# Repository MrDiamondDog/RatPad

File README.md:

# RatPad

My own personal (rat-themed) hackpad! Featuring a decorative 4x4 RGB LED matrix, an informational screen, rats, and a ton of keys to control anything with!

The goal of this project is to learn! I have been wanting experience with PCBs, Fusion, and soldering for a while and this is a good
all-in-one project to get that experience at no cost to me.

Part of Hack Club's Blueprint YSWS.

## Features

- 12 Keys.
- 4x4 RGB LED Matrix.
- 0.91in OLED display.
- Multiple layers, programmable keys, etc.
- LED Matrix for cool decoration. No practical purpose.
- A rat drawn on the silkscreen of the PCB.
- Black + Blue theme
- KMK Firmware

## Todo

- [x] Schematic
- [x] Routing PCB
- [x] Case Design
- [x] Basic Firmware
- [ ] Get Physical Items
- [ ] Solder PCB
- [ ] Finished Build!

## PCB

Here's the schematic and routed PCB! There's a lot of stuff on the silkscreen for fun and the LEDs and keys are both routed in matrices to save on GPIOs! In fact, I have one GPIO available still!

I decided to do chamfered edges on all the corners, with a big one in the lower left since I had extra space and figured it would look nice.

I've also included M3 screw holes, I don't think I'll be using them though.

I definitely should have added a ground plane, but it should be fine.

## Case

Here's all the images of the case! There's a window on the left of the lid to see all the interesting electronics, silkscreen, and LED matrix, a hole for the OLED, and all the holes for the keys.

The chamfered edges from the PCB are reflected on the case as well.

The lid is held on with 4 M3 screws.

I would love to add some acrylic to the window and/or oled, but I don't have access to a laser cutter or any acrylic in the first place.

## BOM

| Item | Quantity |
| ---- | -------- |
| PCB | 1 |
| Through-Hole Seeed XIAO RP2040 | 1 |
| MX Style Switches | 12 |
| DSA Keycaps | 12 |
| Through-Hole IN4148 Diodes | 12 |
| 0.91in OLED I2C Display | 1 |
| SK6812 MINI-E LEDs | 16 |
| M3x16mm Screws | 4 |
| 3d Printed Parts (case + lid) | 2 |

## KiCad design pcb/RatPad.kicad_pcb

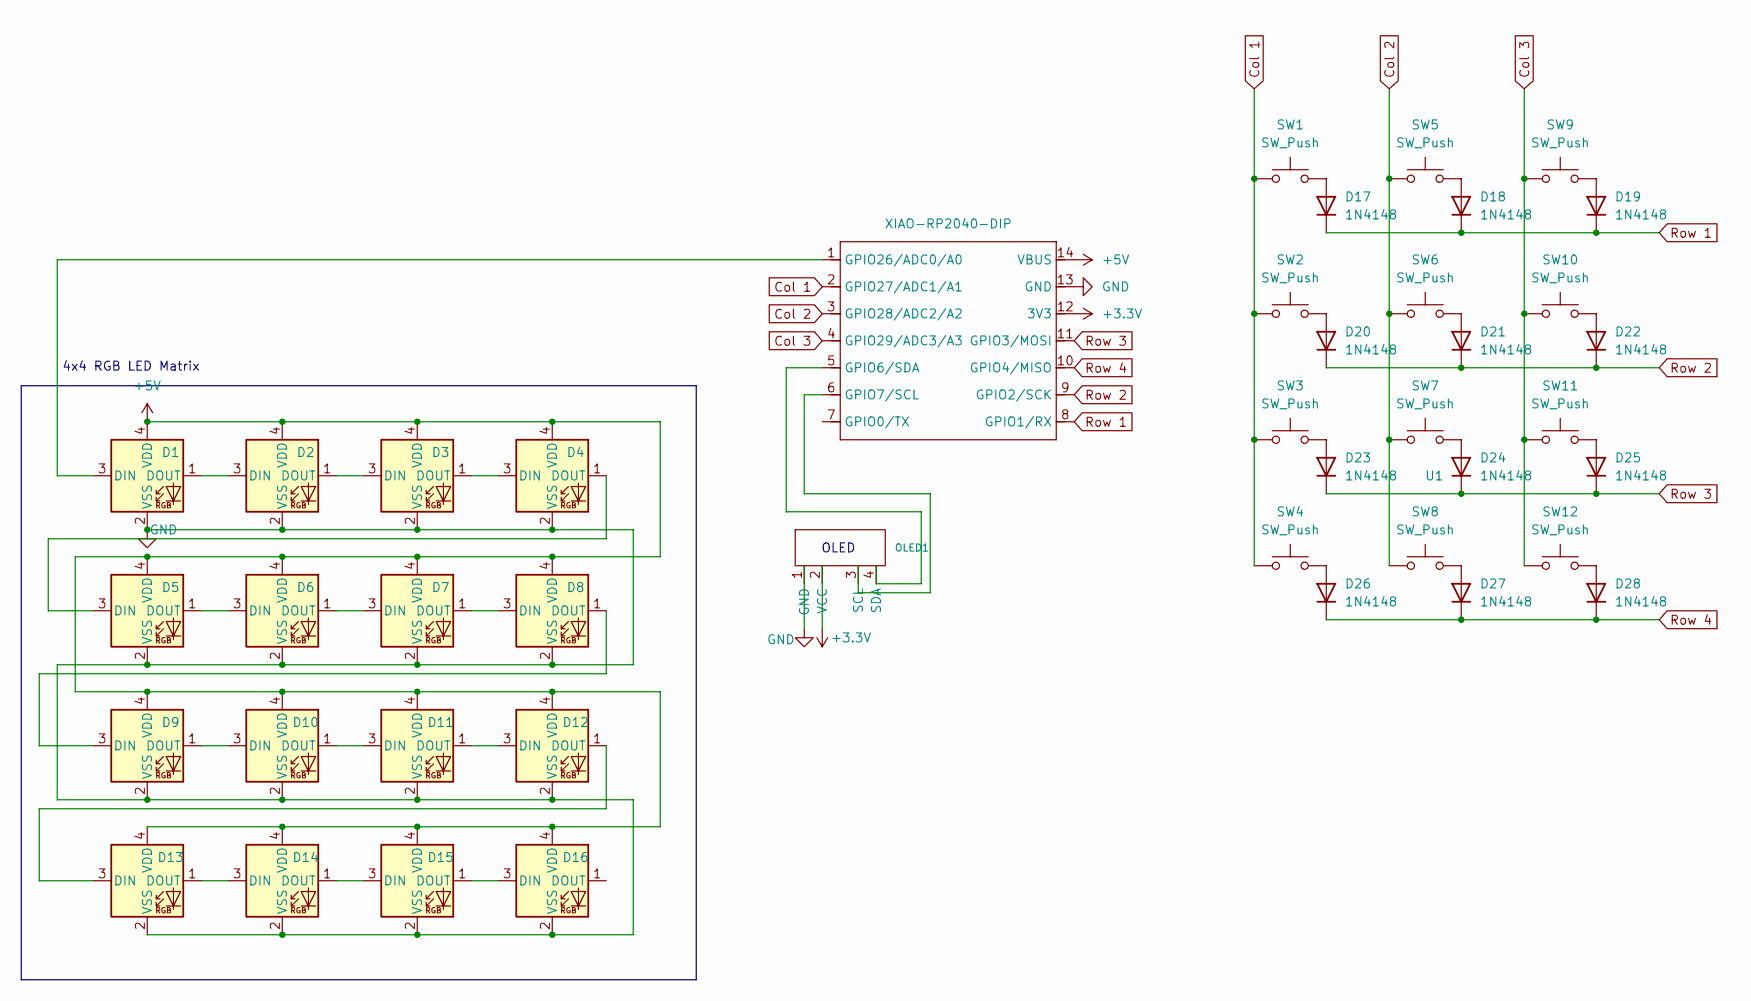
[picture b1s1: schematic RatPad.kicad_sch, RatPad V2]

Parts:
D1, D2, D3, D4, D5, D6, D7, D8, D9, D10, D11, D12, D13, D14, D15, D16: SK6812MINI; LED_SK6812MINI_PLCC4_3.5x3.5mm_P1.75mm
D17, D18, D19, D20, D21, D22, D23, D24, D25, D26, D27, D28: 1N4148; D_DO-35_SOD27_P7.62mm_Horizontal
OLED1: SSD1306-0.91-OLED-4pin-128x32
SW1, SW2, SW3, SW4, SW5, SW6, SW7, SW8, SW9, SW10, SW11, SW12: SW_Push; SW_Cherry_MX_1.00u_PCB
U1: XIAO-RP2040-DIP

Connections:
+3.3V: OLED1.2 (VCC), U1.12 (3V3)
+5V: D1.4 (VDD), D2.4 (VDD), D3.4 (VDD), D4.4 (VDD), D5.4 (VDD), D6.4 (VDD), D7.4 (VDD), D8.4 (VDD), D9.4 (VDD), D10.4 (VDD), D11.4 (VDD), D12.4 (VDD), D13.4 (VDD), D14.4 (VDD), D15.4 (VDD), D16.4 (VDD), U1.14 (VBUS)
Col 1: SW1.1, SW2.1, SW3.1, SW4.1, U1.2 (GPIO27/ADC1/A1)
Col 2: SW5.1, SW6.1, SW7.1, SW8.1, U1.3 (GPIO28/ADC2/A2)
Col 3: SW9.1, SW10.1, SW11.1, SW12.1, U1.4 (GPIO29/ADC3/A3)
GND: D1.2 (VSS), D2.2 (VSS), D3.2 (VSS), D4.2 (VSS), D5.2 (VSS), D6.2 (VSS), D7.2 (VSS), D8.2 (VSS), D9.2 (VSS), D10.2 (VSS), D11.2 (VSS), D12.2 (VSS), D13.2 (VSS), D14.2 (VSS), D15.2 (VSS), D16.2 (VSS), OLED1.1 (GND), U1.13 (GND)
unnamed: D1.3 (DIN), U1.1 (GPIO26/ADC0/A0)
unnamed: D1.1 (DOUT), D2.3 (DIN)
unnamed: D2.1 (DOUT), D3.3 (DIN)
unnamed: D3.1 (DOUT), D4.3 (DIN)
unnamed: D4.1 (DOUT), D5.3 (DIN)
unnamed: D5.1 (DOUT), D6.3 (DIN)
unnamed: D6.1 (DOUT), D7.3 (DIN)
unnamed: D7.1 (DOUT), D8.3 (DIN)
unnamed: D8.1 (DOUT), D9.3 (DIN)
unnamed: D9.1 (DOUT), D10.3 (DIN)
unnamed: D10.1 (DOUT), D11.3 (DIN)
unnamed: D11.1 (DOUT), D12.3 (DIN)
unnamed: D12.1 (DOUT), D13.3 (DIN)
unnamed: D13.1 (DOUT), D14.3 (DIN)
unnamed: D14.1 (DOUT), D15.3 (DIN)
unnamed: D15.1 (DOUT), D16.3 (DIN)
unnamed: D17.2 (A), SW1.2
unnamed: D18.2 (A), SW5.2
unnamed: D19.2 (A), SW9.2
unnamed: D20.2 (A), SW2.2
unnamed: D21.2 (A), SW6.2
unnamed: D22.2 (A), SW10.2
unnamed: D23.2 (A), SW3.2
unnamed: D24.2 (A), SW7.2
unnamed: D25.2 (A), SW11.2
unnamed: D26.2 (A), SW4.2
unnamed: D27.2 (A), SW8.2
unnamed: D28.2 (A), SW12.2
unnamed: OLED1.3 (SCL), U1.6 (GPIO7/SCL)
unnamed: OLED1.4 (SDA), U1.5 (GPIO6/SDA)
Row 1: D17.1 (K), D18.1 (K), D19.1 (K), U1.8 (GPIO1/RX)
Row 2: D20.1 (K), D21.1 (K), D22.1 (K), U1.9 (GPIO2/SCK)
Row 3: D23.1 (K), D24.1 (K), D25.1 (K), U1.11 (GPIO3/MOSI)
Row 4: D26.1 (K), D27.1 (K), D28.1 (K), U1.10 (GPIO4/MISO)

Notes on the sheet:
4x4 RGB LED Matrix
OLED

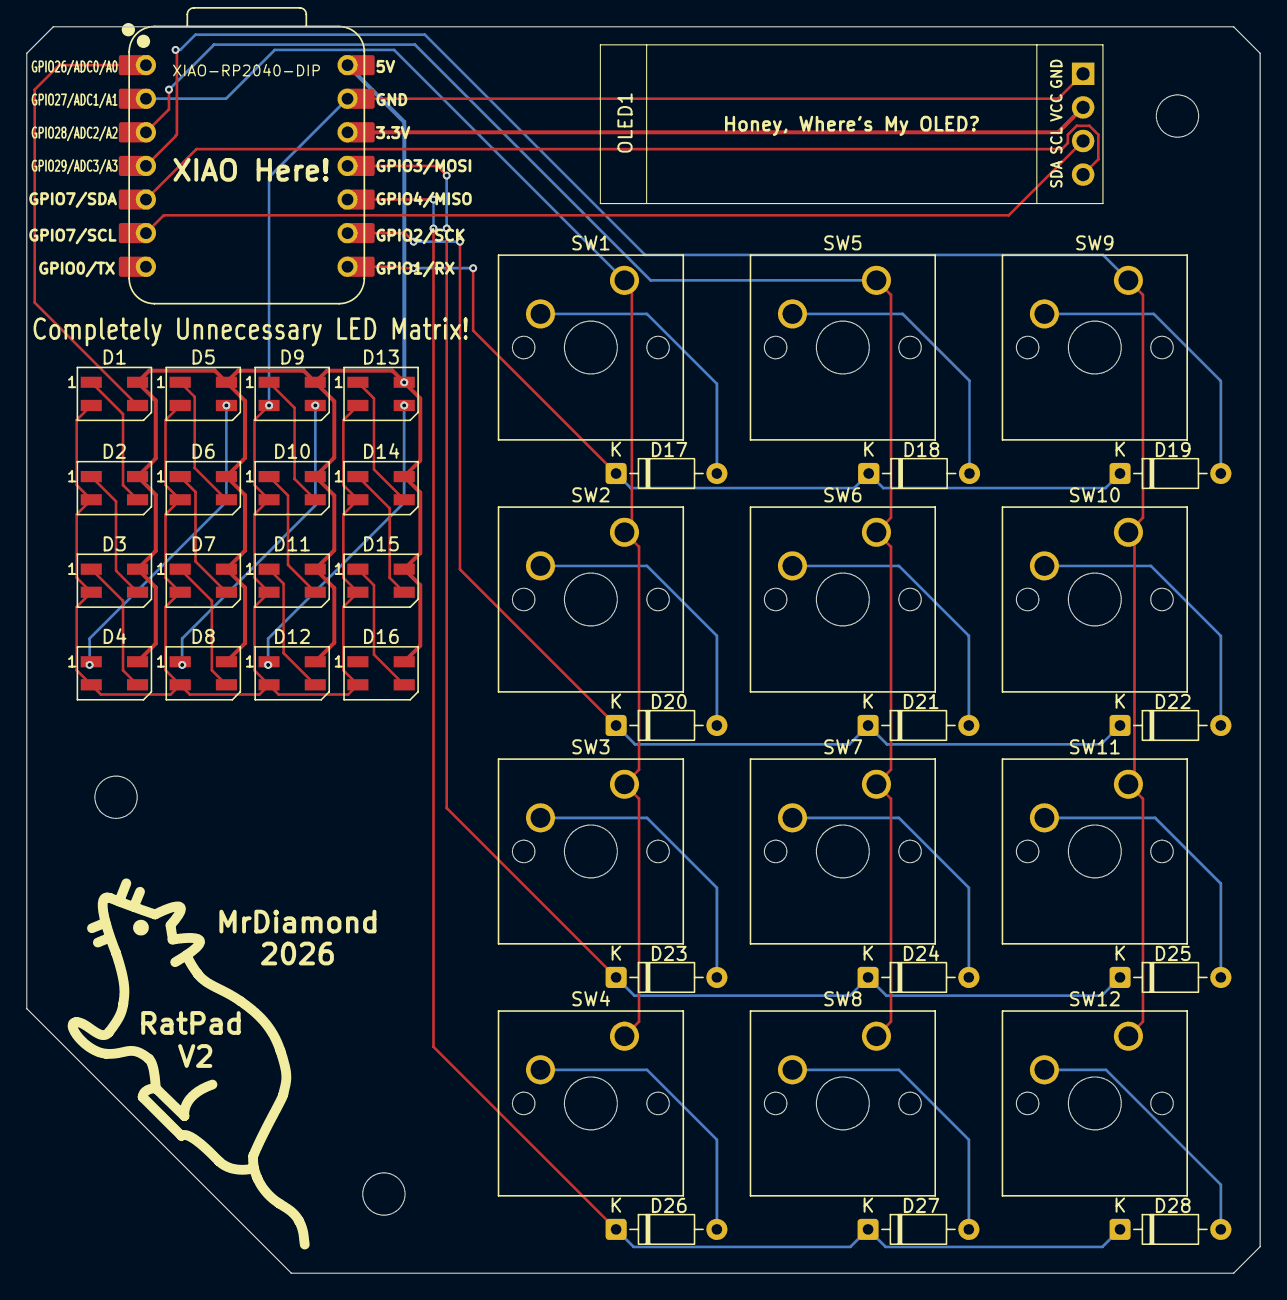
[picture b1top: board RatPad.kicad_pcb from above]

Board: 2 copper layers, 93.2 x 94.2 mm, 42 parts (0 on the bottom side), 40 nets.

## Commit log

2025-12-29 Init
2025-12-29 Add README.md and Images
2025-12-29 Fix Formatting
2025-12-30 Add case and update PCB
2025-12-30 Fix README images
2025-12-30 Basic Firmware!
2025-12-30 Update README for submission
